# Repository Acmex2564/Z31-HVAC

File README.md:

# Z31-HVAC

This sure is a thing

36 pin board connector is TE 172023-1 Dual-Line Interlock (DLI). Same connector as on ECU. Same connector series as TCU, ASCD, Suspension Controller, DD Power Supply. 

5 pin board connector is TE 172040-1 - Multi Interlock Connector (MIC) Mk II.

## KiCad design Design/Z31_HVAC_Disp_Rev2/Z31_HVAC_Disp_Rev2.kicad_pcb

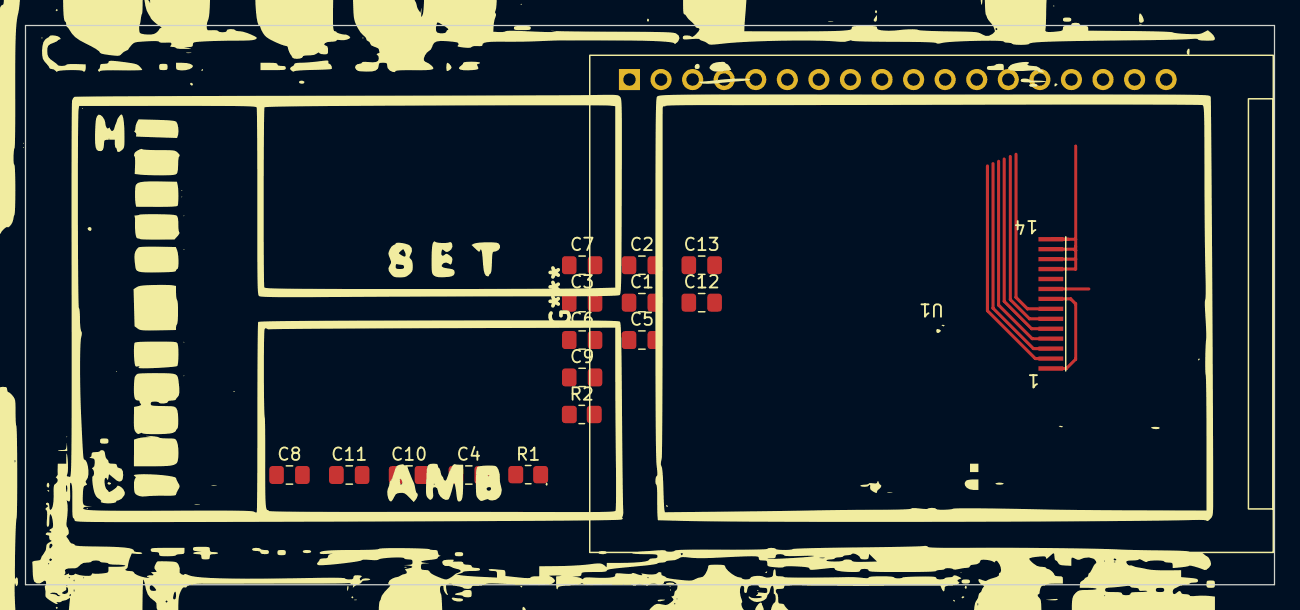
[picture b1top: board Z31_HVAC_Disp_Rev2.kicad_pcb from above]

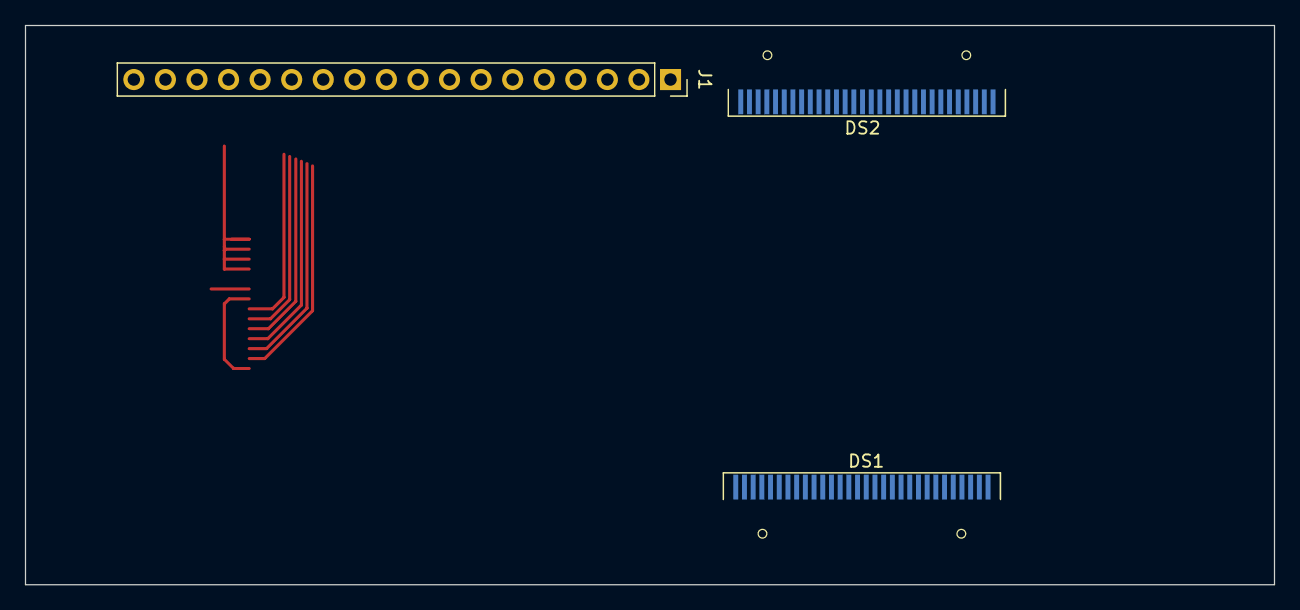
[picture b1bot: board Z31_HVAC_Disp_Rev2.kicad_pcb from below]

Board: 2 copper layers, 100.5 x 45.0 mm, 19 parts (3 on the bottom side), 26 nets.

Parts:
C1, C2, C5, C6, C8, C9, C11, C12: 1u; C_0805_2012Metric_Pad1.18x1.45mm_HandSolder
C3, C10: 4.7u; C_0805_2012Metric_Pad1.18x1.45mm_HandSolder
C4: 100n; C_0805_2012Metric_Pad1.18x1.45mm_HandSolder
C7, C13: 2.2u; C_0805_2012Metric_Pad1.18x1.45mm_HandSolder
DS1, DS2: OLED-128O064D
J1: Conn_01x18; PinSocket_1x18_P2.54mm_Vertical
R1, R2: 390k; R_0805_2012Metric_Pad1.20x1.40mm_HandSolder
U1: 2.2__WVGA_SPI_14pin; 2.2_wvga_spi

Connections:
+3V3: C4.1, C5.1, C6.1, C11.1, C12.1, DS1.6 (VBAT), DS1.9 (VDD), DS2.6 (VBAT), DS2.9 (VDD), J1.2, U1.9 (VCC)
/CS1: DS1.13 (~CS), J1.10
/CS2: DS2.13 (~CS), J1.9
/CS3: J1.8, U1.5 (CS)
/D/C: DS1.15 (D/~C), DS2.15 (D/~C), J1.6, U1.4 (D/CX)
/RESET1: DS1.14 (~RES), J1.13
/RESET2: DS2.14 (~RES), J1.12
/RESET3: J1.11, U1.2 (RESET)
/SCK: DS1.18 (D0), DS2.18 (D0), J1.3, U1.3 (SCL)
/SDI: DS1.19 (D1), DS2.19 (D1), J1.4, U1.6 (SDI)
/SDO: J1.5, U1.7 (SDO)
GND: C3.2, C4.2, C5.2, C6.2, C7.2, C10.2, C11.2, C12.2, C13.2, DS1.1 (GND), DS1.8 (VSS), DS1.10 (BS0), DS1.11 (BS1), DS1.12 (BS2), DS1.16 (R/~W), DS1.17 (E/~RD), DS1.21 (D3), DS1.22 (D4), DS1.23 (D5), DS1.24 (D6), DS1.25 (D7), DS1.29 (VLSS), DS1.30 (GND), DS2.1 (GND), DS2.8 (VSS), DS2.10 (BS0), DS2.11 (BS1), DS2.12 (BS2), DS2.16 (R/~W), DS2.17 (E/~RD), DS2.21 (D3), DS2.22 (D4), DS2.23 (D5), DS2.24 (D6), DS2.25 (D7), DS2.29 (VLSS), DS2.30 (GND), J1.1, J1.18, R1.2, R2.2, U1.1 (GND_P), U1.8 (GND), U1.11 (LEDK1), U1.12 (LEDK2), U1.13 (LEDK3), U1.14 (LEDK4)
unnamed: C1.1, DS1.2 (C2N)
unnamed: C1.2, DS1.3 (C2P)
unnamed: C2.1, DS1.4 (C1P)
unnamed: C2.2, DS1.5 (C1N)
unnamed: C3.1, DS1.27 (VCOMH)
unnamed: C7.1, DS1.28 (VCC)
unnamed: C8.1, DS2.2 (C2N)
unnamed: C8.2, DS2.3 (C2P)
unnamed: C9.1, DS2.4 (C1P)
unnamed: C9.2, DS2.5 (C1N)
unnamed: C10.1, DS2.27 (VCOMH)
unnamed: C13.1, DS2.28 (VCC)
unnamed: DS1.26 (IREF), R1.1
unnamed: DS2.26 (IREF), R2.1

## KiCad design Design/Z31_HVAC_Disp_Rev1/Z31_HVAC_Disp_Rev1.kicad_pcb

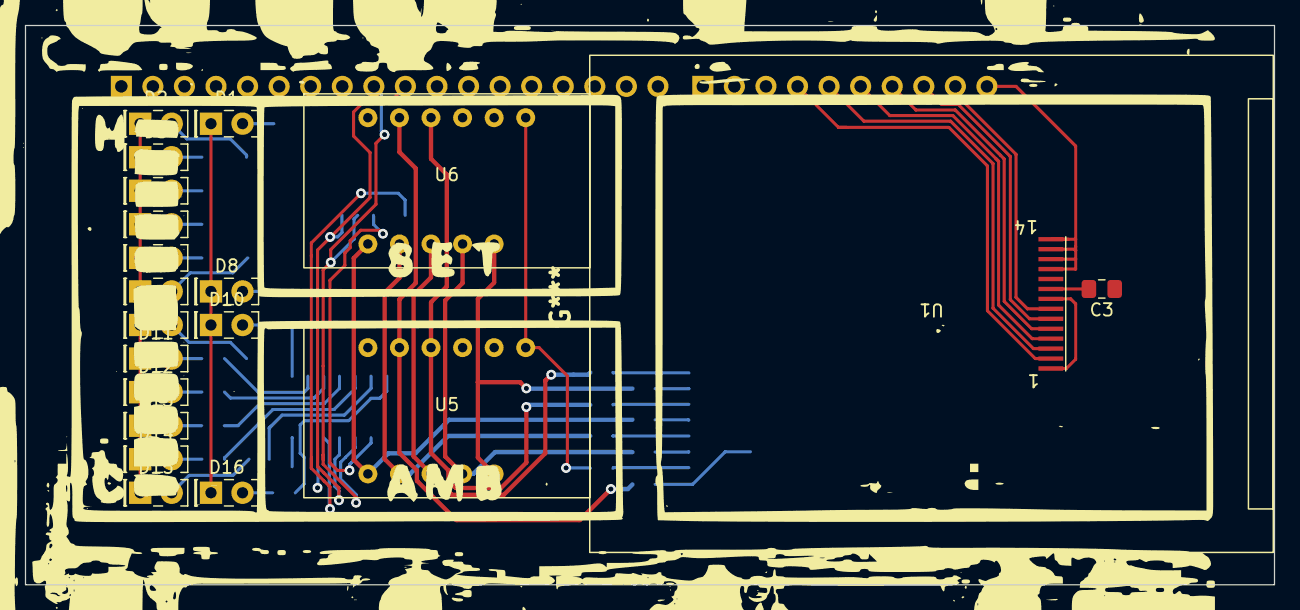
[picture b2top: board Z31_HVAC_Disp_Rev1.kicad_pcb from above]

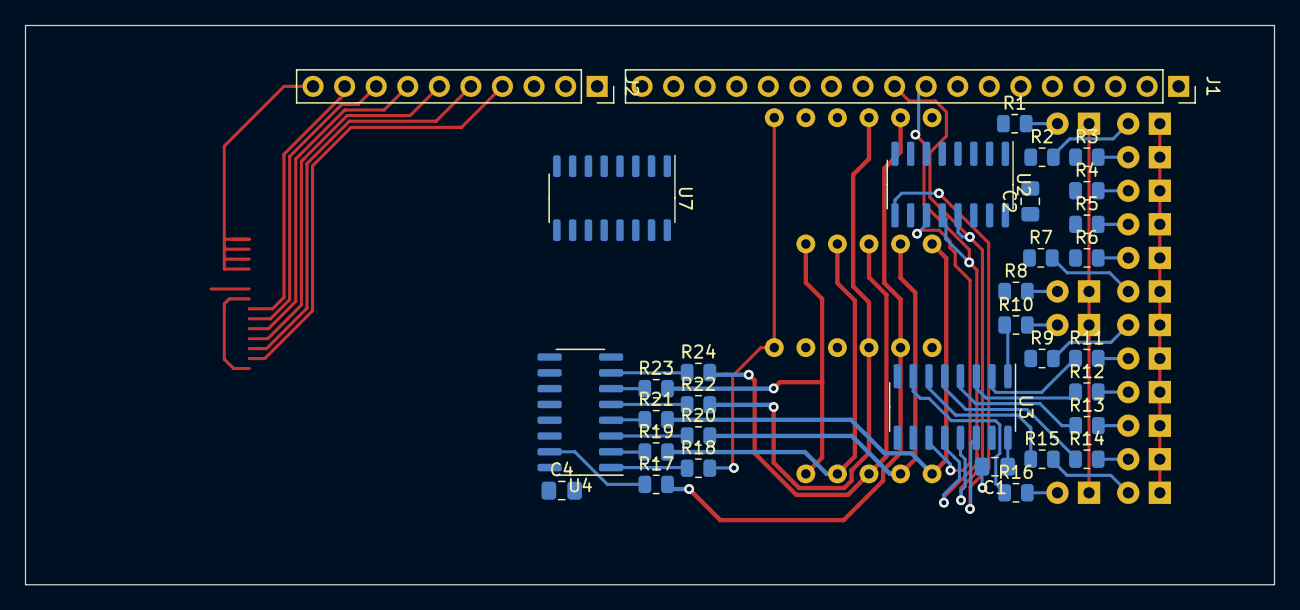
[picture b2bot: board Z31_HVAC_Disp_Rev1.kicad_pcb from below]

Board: 2 copper layers, 100.5 x 45.0 mm, 53 parts (33 on the bottom side), 79 nets.

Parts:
C1, C2, C3, C4: 100n; C_0805_2012Metric_Pad1.18x1.45mm_HandSolder
D1, D2, D3, D4, D5, D6, D7, D8, D9, D10, D11, D12, D13, D14, D15, D16: LED; LED_Rectangular_W5.0mm_H2.0mm
J1: Conn_01x18; PinSocket_1x18_P2.54mm_Vertical
J2: Conn_01x10; PinSocket_1x10_P2.54mm_Vertical
R1, R2, R3, R4, R5, R6, R7, R8, R9, R10, R11, R12, R13, R14, R15, R16, R17, R18, R19, R20, R21, R22, R23, R24: 220; R_0805_2012Metric
U1: 2.2__WVGA_SPI_14pin; 2.2_wvga_spi
U2, U3, U4: 74HC595; SOIC-16_3.9x9.9mm_P1.27mm
U5, U6: CL3631AH
U7: ULN2003; SO-16_3.9x9.9mm_P1.27mm

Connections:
+5V: C1.1, C2.1, C4.1, J1.2, U2.16 (VCC), U3.16 (VCC), U4.16 (VCC)
/Clear: J1.5, U2.10 (~SRCLR), U3.10 (~SRCLR), U4.10 (~SRCLR)
/D1: J1.11, U7.1 (I1)
/D2: J1.12, U7.2 (I2)
/D3: J1.13, U7.3 (I3)
/D4: J1.14, U7.4 (I4)
/D5: J1.15, U7.5 (I5)
/D6: J1.16, U7.6 (I6)
/LED_Dimming: J1.10, U2.13 (~OE), U3.13 (~OE), U4.13 (~OE)
/LH_1: J1.9, U2.12 (RCLK), U3.12 (RCLK)
/LH_2: J1.6, U4.12 (RCLK)
/MOSI_1: J1.7, U2.14 (SER)
/MOSI_2: J1.3, U4.14 (SER)
/SCK_1: J1.8, U2.11 (SRCLK), U3.11 (SRCLK)
/SCK_2: J1.4, U4.11 (SRCLK)
GND: C1.2, C2.2, C3.1, C4.2, D1.1 (K), D2.1 (K), D3.1 (K), D4.1 (K), D5.1 (K), D6.1 (K), D7.1 (K), D8.1 (K), D9.1 (K), D10.1 (K), D11.1 (K), D12.1 (K), D13.1 (K), D14.1 (K), D15.1 (K), D16.1 (K), J1.1, J1.18, J2.1, J2.10, U1.1 (GND_P), U1.8 (GND), U1.11 (LEDK1), U1.12 (LEDK2), U1.13 (LEDK3), U1.14 (LEDK4), U2.8 (GND), U3.8 (GND), U4.8 (GND), U7.8 (GND)
unnamed: C3.2, J2.2, U1.9 (VCC)
unnamed: D1.2 (A), R1.2
unnamed: D2.2 (A), R2.2
unnamed: D3.2 (A), R3.2
unnamed: D4.2 (A), R4.2
unnamed: D5.2 (A), R5.2
unnamed: D6.2 (A), R6.2
unnamed: D7.2 (A), R7.2
unnamed: D8.2 (A), R8.2
unnamed: D9.2 (A), R9.2
unnamed: D10.2 (A), R10.2
unnamed: D11.2 (A), R11.2
unnamed: D12.2 (A), R12.2
unnamed: D13.2 (A), R13.2
unnamed: D14.2 (A), R14.2
unnamed: D15.2 (A), R15.2
unnamed: D16.2 (A), R16.2
unnamed: J2.3, U1.10 (LEDA)
unnamed: J2.4, U1.2 (RESET)
unnamed: J2.5, U1.3 (SCL)
unnamed: J2.6, U1.4 (D/CX)
unnamed: J2.7, U1.5 (CS)
unnamed: J2.8, U1.6 (SDI)
unnamed: J2.9, U1.7 (SDO)
unnamed: R1.1, U2.15 (QA)
unnamed: R2.1, U2.1 (QB)
unnamed: R3.1, U2.2 (QC)
unnamed: R4.1, U2.3 (QD)
unnamed: R5.1, U2.4 (QE)
unnamed: R6.1, U2.5 (QF)
unnamed: R7.1, U2.6 (QG)
unnamed: R8.1, U2.7 (QH)
unnamed: R9.1, U3.15 (QA)
unnamed: R10.1, U3.1 (QB)
unnamed: R11.1, U3.2 (QC)
unnamed: R12.1, U3.3 (QD)
unnamed: R13.1, U3.4 (QE)
unnamed: R14.1, U3.5 (QF)
unnamed: R15.1, U3.6 (QG)
unnamed: R16.1, U3.7 (QH)
unnamed: R17.1, U4.15 (QA)
unnamed: R17.2, U5.11 (ANODE_A), U6.11 (ANODE_A)
unnamed: R18.1, U4.1 (QB)
unnamed: R18.2, U5.7 (ANODE_B), U6.7 (ANODE_B)
unnamed: R19.1, U4.2 (QC)
unnamed: R19.2, U5.4 (ANODE_C), U6.4 (ANODE_C)
unnamed: R20.1, U4.3 (QD)
unnamed: R20.2, U5.2 (ANODE_D), U6.2 (ANODE_D)
unnamed: R21.1, U4.4 (QE)
unnamed: R21.2, U5.1 (ANODE_E), U6.1 (ANODE_E)
unnamed: R22.1, U4.5 (QF)
unnamed: R22.2, U5.10 (ANODE_F), U6.10 (ANODE_F)
unnamed: R23.1, U4.6 (QG)
unnamed: R23.2, U5.5 (ANODE_G), U6.5 (ANODE_G)
unnamed: R24.1, U4.7 (QH)
unnamed: R24.2, U5.3 (ANODE_DP), U6.3 (ANODE_DP)
unnamed: U2.9 (QH'), U3.14 (SER)
unnamed: U5.8 (CATHODE_3), U7.16 (O1)
unnamed: U5.9 (CATHODE_2), U7.15 (O2)
unnamed: U5.12 (CATHODE_1), U7.14 (O3)
unnamed: U6.8 (CATHODE_3), U7.13 (O4)
unnamed: U6.9 (CATHODE_2), U7.12 (O5)
unnamed: U6.12 (CATHODE_1), U7.11 (O6)

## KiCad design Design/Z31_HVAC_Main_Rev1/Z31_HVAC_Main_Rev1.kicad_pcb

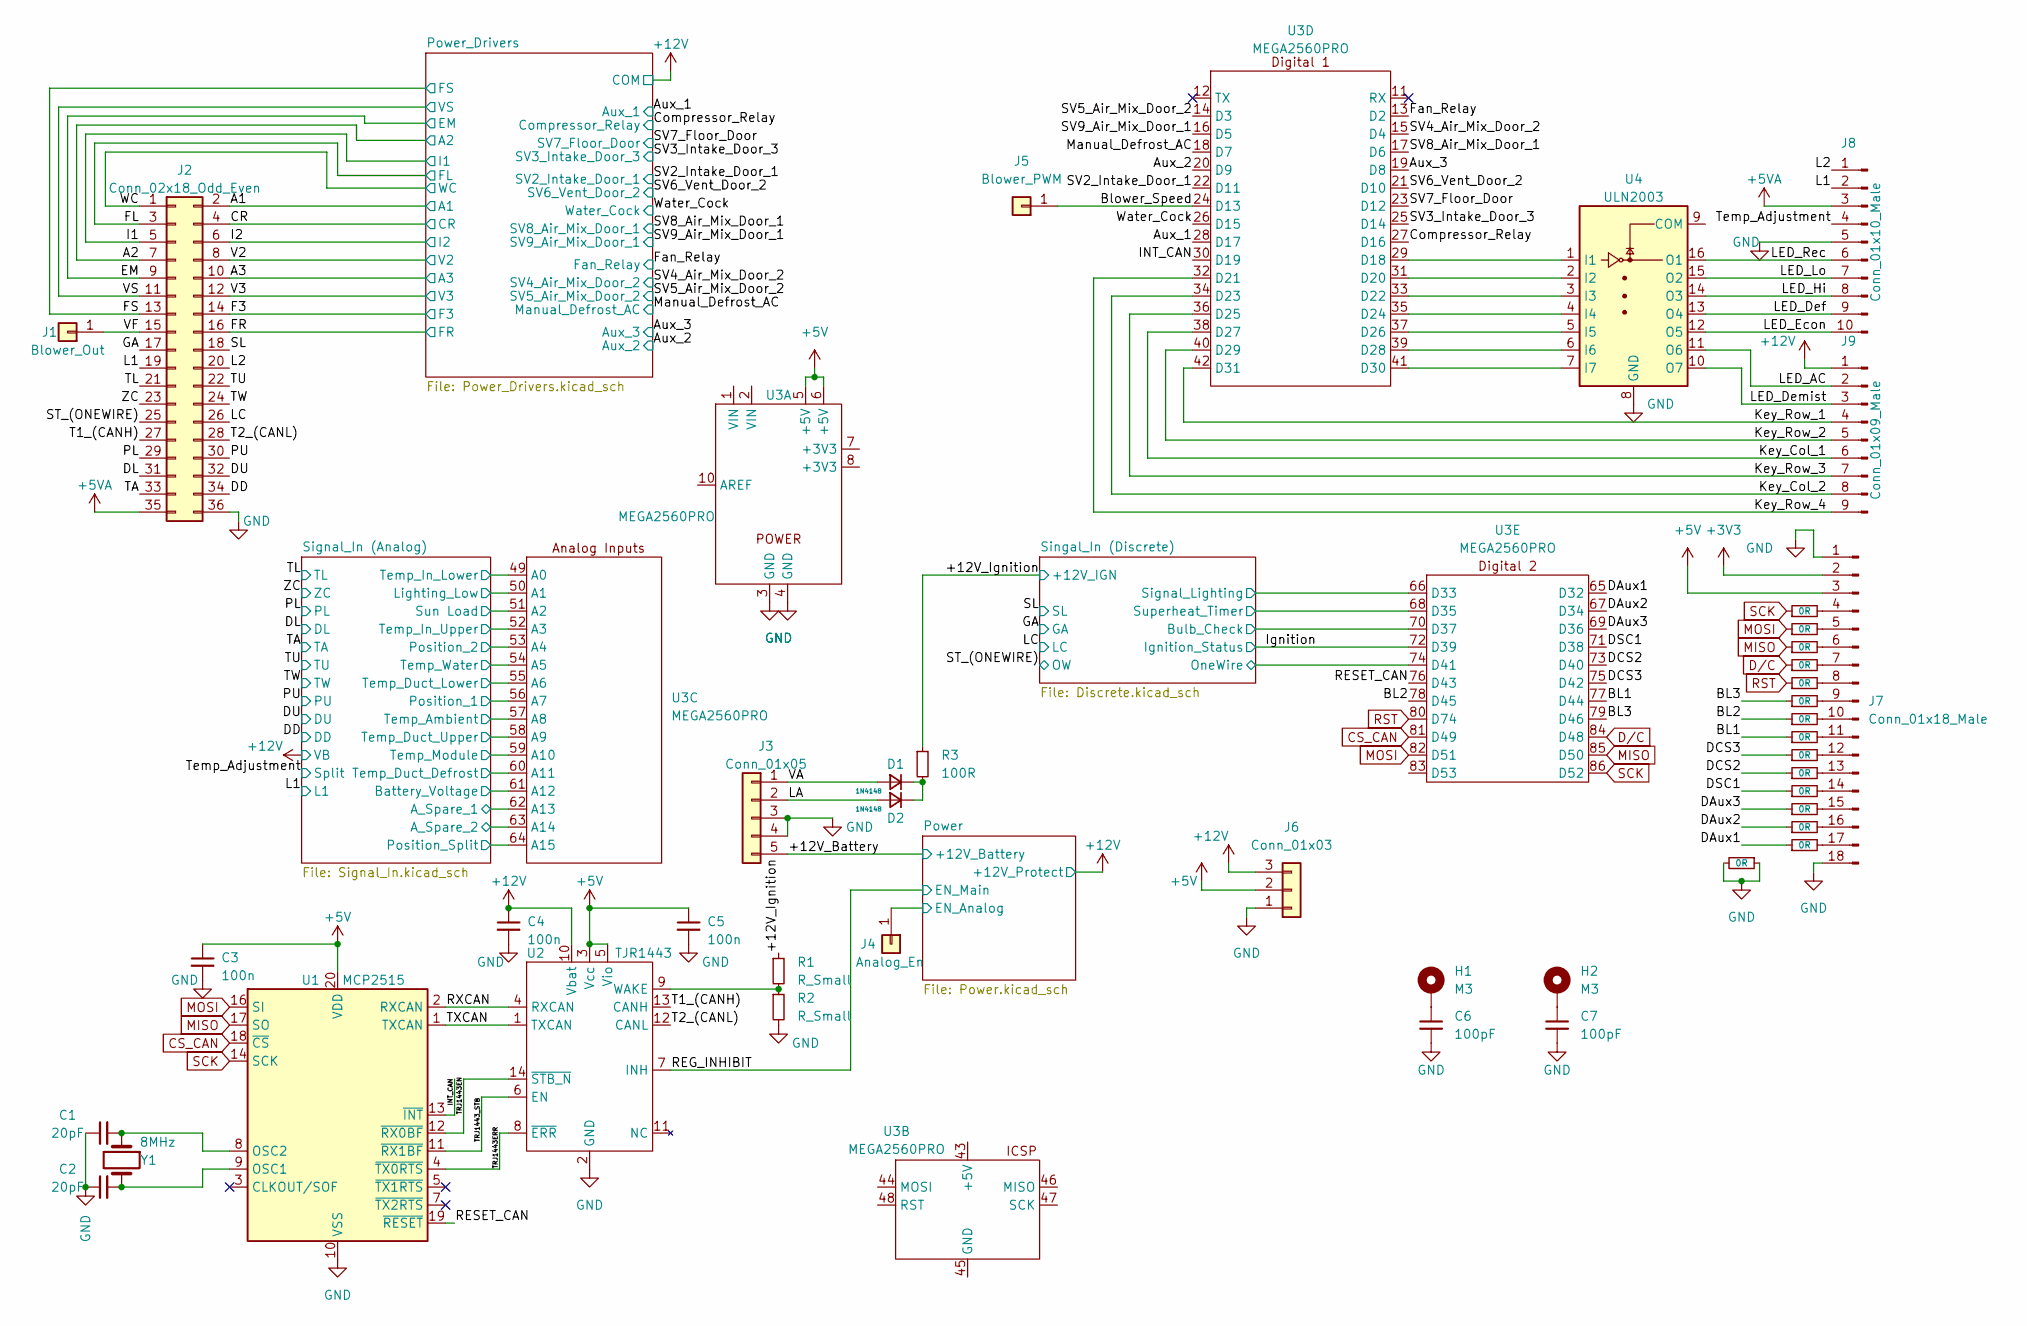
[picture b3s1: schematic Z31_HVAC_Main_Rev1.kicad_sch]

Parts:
C1, C2: 20pF; C_0805_2012Metric_Pad1.18x1.45mm_HandSolder
C3, C4, C5: 100n; C_0805_2012Metric_Pad1.18x1.45mm_HandSolder
C6, C7: 100pF; C_0805_2012Metric_Pad1.18x1.45mm_HandSolder
D1, D2: 1N4148; D_SOD-323_HandSoldering
H1, H2: M3; MountingHole_3.5mm_Pad
J1: Blower_Out; PinHeader_1x01_P2.54mm_Vertical
J2: Conn_02x18_Odd_Even; TE-172023
J3: Conn_01x05; Z31_HVAC_Connector_1
J4: Analog_En; PinHeader_1x01_P2.54mm_Vertical
J5: Blower_PWM; PinHeader_1x01_P2.54mm_Vertical
J6: Conn_01x03; Proto-Area
J7: Conn_01x18_Male; PinHeader_1x18_P2.54mm_Vertical
J8: Conn_01x10_Male; PinHeader_1x10_P2.54mm_Vertical
J9: Conn_01x09_Male; PinHeader_1x09_P2.54mm_Vertical
R1, R2: R_Small; R_0805_2012Metric_Pad1.20x1.40mm_HandSolder
R3: 100R; R_Axial_DIN0207_L6.3mm_D2.5mm_P7.62mm_Horizontal
R4, R5, R6, R7, R8, R9, R10, R11, R12, R13, R14, R15, R16, R17, R18: 0R; R_Axial_DIN0204_L3.6mm_D1.6mm_P2.54mm_Vertical
U1: MCP2515; TSSOP-20_4.4x6.5mm_P0.65mm
U2: TJR1443; SO-14_3.9x8.65mm_P1.27mm
U3: MEGA2560PRO
U4: ULN2003; SO-16_3.9x9.9mm_P1.27mm
Y1: 8MHz; Crystal_SMD_HC49-SD

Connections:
+3V3: J7.2
+5V: C3.1, C5.1, J6.2, J7.3, U1.20 (VDD), U2.3 (Vcc), U2.5 (Vio), U3.5 (+5V), U3.6 (+5V); also elsewhere on the board
+5VA: J2.35, J8.3; also elsewhere on the board
+12V: C4.1, J6.3, J9.1, U2.10 (Vbat); also elsewhere on the board
/+12V_Battery: J3.5; also elsewhere on the board
/+12V_Ignition: R1.1, R3.1; also elsewhere on the board
/A1: J2.2; also elsewhere on the board
/A2: J2.7; also elsewhere on the board
/A3: J2.10; also elsewhere on the board
/Aux_1: U3.28 (D17); also elsewhere on the board
/Aux_2: U3.20 (D9); also elsewhere on the board
/Aux_3: U3.19 (D8); also elsewhere on the board
/BL1: R12.1, U3.77 (D44)
/BL2: R11.1, U3.78 (D45)
/BL3: R10.1, U3.79 (D46)
/Blower_Speed: J5.1, U3.24 (D13)
/CR: J2.4; also elsewhere on the board
/Compressor_Relay: U3.27 (D16); also elsewhere on the board
/DAux1: R18.1, U3.65 (D32)
/DAux2: R17.1, U3.67 (D34)
/DAux3: R16.1, U3.69 (D36)
/DCS2: R14.1, U3.73 (D40)
/DCS3: R13.1, U3.75 (D42)
/DD: J2.34; also elsewhere on the board
/DL: J2.31; also elsewhere on the board
/DSC1: R15.1, U3.71 (D38)
/DU: J2.32; also elsewhere on the board
/EM: J2.9; also elsewhere on the board
/F3: J2.14; also elsewhere on the board
/FL: J2.3; also elsewhere on the board
/FR: J2.16; also elsewhere on the board
/FS: J2.13; also elsewhere on the board
/Fan_Relay: U3.13 (D2); also elsewhere on the board
/GA: J2.17; also elsewhere on the board
/I1: J2.5; also elsewhere on the board
/I2: J2.6; also elsewhere on the board
/INT_CAN: U1.13 (~INT), U3.30 (D19)
/Ignition: U3.72 (D39); also elsewhere on the board
/Key_Col_1: J9.6, U3.38 (D27)
/Key_Col_2: J9.8, U3.34 (D23)
/Key_Row_1: J9.4, U3.42 (D31)
/Key_Row_2: J9.5, U3.40 (D29)
/Key_Row_3: J9.7, U3.36 (D25)
/Key_Row_4: J9.9, U3.32 (D21)
/L1: J2.19, J8.2; also elsewhere on the board
/L2: J2.20, J8.1
/LA: D2.2 (A), J3.2
/LC: J2.26; also elsewhere on the board
/LED_AC: J9.2, U4.11 (O6)
/LED_Def: J8.9, U4.13 (O4)
/LED_Demist: J9.3, U4.10 (O7)
/LED_Econ: J8.10, U4.12 (O5)
/LED_Hi: J8.8, U4.14 (O3)
/LED_Lo: J8.7, U4.15 (O2)
/LED_Rec: J8.6, U4.16 (O1)
/Manual_Defrost_AC: U3.18 (D7); also elsewhere on the board
/PL: J2.29; also elsewhere on the board
/PU: J2.30; also elsewhere on the board
/Power/EN_Analog: J4.1; also elsewhere on the board
/REG_INHIBIT: U2.7 (INH); also elsewhere on the board
/RESET_CAN: U1.19 (~RESET), U3.76 (D43)
/RXCAN: U1.2 (RXCAN), U2.4 (RXCAN)
/SL: J2.18; also elsewhere on the board
/ST_(ONEWIRE): J2.25; also elsewhere on the board
/SV2_Intake_Door_1: U3.22 (D11); also elsewhere on the board
/SV3_Intake_Door_3: U3.25 (D14); also elsewhere on the board
/SV4_Air_Mix_Door_2: U3.15 (D4); also elsewhere on the board
/SV5_Air_Mix_Door_2: U3.14 (D3); also elsewhere on the board
/SV6_Vent_Door_2: U3.21 (D10); also elsewhere on the board
/SV7_Floor_Door: U3.23 (D12); also elsewhere on the board
/SV8_Air_Mix_Door_1: U3.17 (D6); also elsewhere on the board
/SV9_Air_Mix_Door_1: U3.16 (D5); also elsewhere on the board
/Signal_In (Analog)/A_Spare_1: U3.62 (A13); also elsewhere on the board
/Signal_In (Analog)/A_Spare_2: U3.63 (A14); also elsewhere on the board
/Signal_In (Analog)/Battery_Voltage: U3.61 (A12); also elsewhere on the board
/Signal_In (Analog)/Lighting_Low: U3.50 (A1); also elsewhere on the board
/Signal_In (Analog)/Position_1: U3.56 (A7); also elsewhere on the board
/Signal_In (Analog)/Position_2: U3.53 (A4); also elsewhere on the board
/Signal_In (Analog)/Position_Split: U3.64 (A15); also elsewhere on the board
/Signal_In (Analog)/Sun Load: U3.51 (A2); also elsewhere on the board
/Signal_In (Analog)/Temp_Ambient: U3.57 (A8); also elsewhere on the board
/Signal_In (Analog)/Temp_Duct_Defrost: U3.60 (A11); also elsewhere on the board
/Signal_In (Analog)/Temp_Duct_Lower: U3.55 (A6); also elsewhere on the board
/Signal_In (Analog)/Temp_Duct_Upper: U3.58 (A9); also elsewhere on the board
/Signal_In (Analog)/Temp_In_Lower: U3.49 (A0); also elsewhere on the board
/Signal_In (Analog)/Temp_In_Upper: U3.52 (A3); also elsewhere on the board
/Signal_In (Analog)/Temp_Module: U3.59 (A10); also elsewhere on the board
/Signal_In (Analog)/Temp_Water: U3.54 (A5); also elsewhere on the board
/Singal_In (Discrete)/Bulb_Check: U3.70 (D37); also elsewhere on the board
/Singal_In (Discrete)/OneWire: U3.74 (D41); also elsewhere on the board
/Singal_In (Discrete)/Signal_Lighting: U3.66 (D33); also elsewhere on the board
/Singal_In (Discrete)/Superheat_Timer: U3.68 (D35); also elsewhere on the board
/T1_(CANH): J2.27, U2.13 (CANH)
/T2_(CANL): J2.28, U2.12 (CANL)
/TA: J2.33; also elsewhere on the board
/TL: J2.21; also elsewhere on the board
/TRJ1443EN: U1.12 (~RX0BF), U2.14 (~STB_N)
/TRJ1443ERR: U1.4 (~TX0RTS), U2.8 (~ERR)
/TRJ1443_STB: U1.11 (~RX1BF), U2.6 (EN)
/TU: J2.22; also elsewhere on the board
/TW: J2.24; also elsewhere on the board
/TXCAN: U1.1 (TXCAN), U2.1 (TXCAN)
/Temp_Adjustment: J8.4; also elsewhere on the board
/V2: J2.8; also elsewhere on the board
/V3: J2.12; also elsewhere on the board
/VA: D1.2 (A), J3.1
/VF: J1.1, J2.15
/VS: J2.11; also elsewhere on the board
/WC: J2.1; also elsewhere on the board
/Water_Cock: U3.26 (D15); also elsewhere on the board
/ZC: J2.23; also elsewhere on the board
CS_CAN: U1.18 (~CS), U3.81 (D49)
D/C: R8.1, U3.84 (D48)
GND: C1.1, C2.1, C3.2, C4.2, C5.2, C6.2, C7.2, J2.36, J3.3, J3.4, J6.1, J7.1, J7.18, J8.5, R2.2, R4.1, R4.2, U1.10 (VSS), U2.2 (GND), U3.3 (GND), U3.4 (GND), U4.8 (GND); also elsewhere on the board
MISO: R7.1, U1.17 (SO), U3.85 (D50)
MOSI: R6.1, U1.16 (SI), U3.82 (D51)
unnamed: C1.2, U1.8 (OSC2), Y1.1
unnamed: C2.2, U1.9 (OSC1), Y1.2
unnamed: C6.1, H1.1
unnamed: C7.1, H2.1
unnamed: D1.1 (K), D2.1 (K), R3.2
unnamed: J7.4, R5.2
unnamed: J7.5, R6.2
unnamed: J7.6, R7.2
unnamed: J7.7, R8.2
unnamed: J7.8, R9.2
unnamed: J7.9, R10.2
unnamed: J7.10, R11.2
unnamed: J7.11, R12.2
unnamed: J7.12, R13.2
unnamed: J7.13, R14.2
unnamed: J7.14, R15.2
unnamed: J7.15, R16.2
unnamed: J7.16, R17.2
unnamed: J7.17, R18.2
unnamed: R1.2, R2.1, U2.9 (WAKE)
unnamed: U3.29 (D18), U4.1 (I1)
unnamed: U3.31 (D20), U4.2 (I2)
unnamed: U3.33 (D22), U4.3 (I3)
unnamed: U3.35 (D24), U4.4 (I4)
unnamed: U3.37 (D26), U4.5 (I5)
unnamed: U3.39 (D28), U4.6 (I6)
unnamed: U3.41 (D30), U4.7 (I7)
RST: R9.1, U3.80 (D74)
SCK: R5.1, U1.14 (SCK), U3.86 (D52)

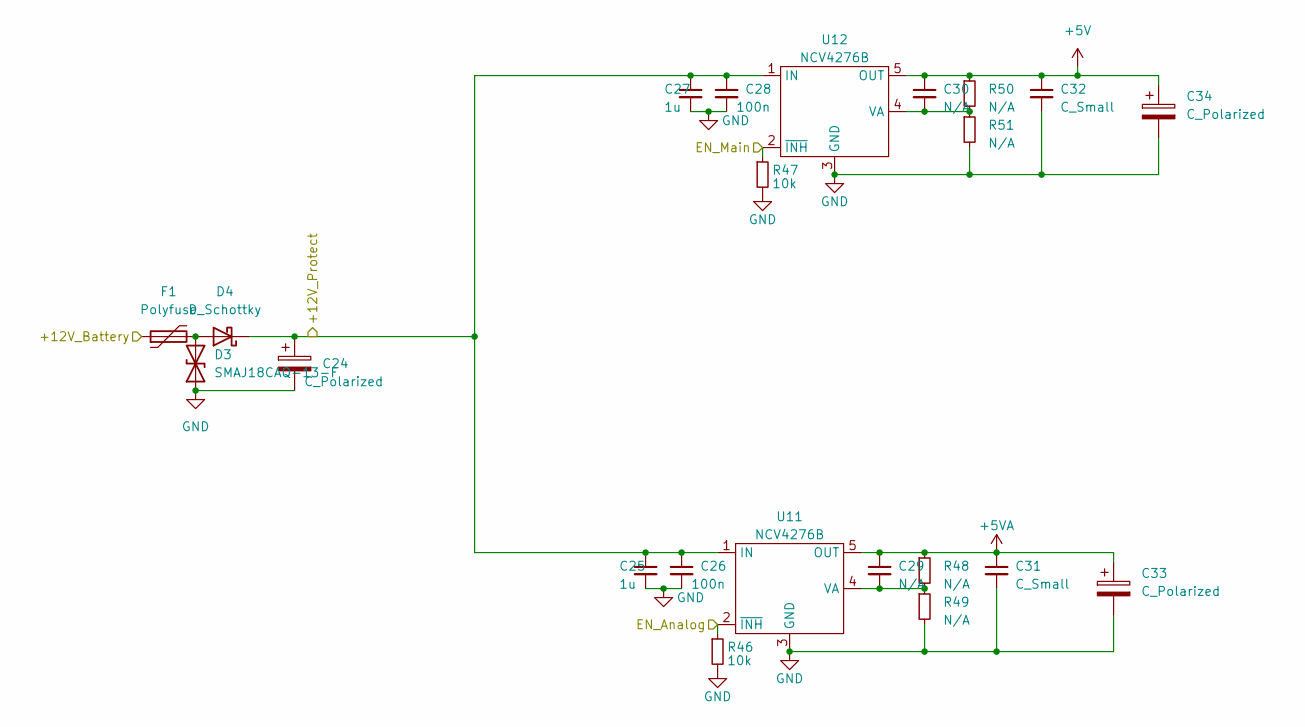
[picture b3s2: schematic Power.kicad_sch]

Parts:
C24: C_Polarized; CP_Radial_D8.0mm_P3.50mm
C25, C27: 1u; C_1210_3225Metric_Pad1.33x2.70mm_HandSolder
C26, C28: 100n; C_0805_2012Metric_Pad1.18x1.45mm_HandSolder
C29, C30: N/A; C_0805_2012Metric_Pad1.18x1.45mm_HandSolder
C31, C32: C_Small; C_1210_3225Metric_Pad1.33x2.70mm_HandSolder
C33, C34: C_Polarized; CP_Elec_5x5.3
D3: SMAJ18CAQ-13-F; D_SMA
D4: D_Schottky; D_SMA
F1: Polyfuse; Fuse_1812_4532Metric_Pad1.30x3.40mm_HandSolder
R46, R47: 10k; R_0805_2012Metric_Pad1.20x1.40mm_HandSolder
R48, R49, R50, R51: N/A; R_0805_2012Metric_Pad1.20x1.40mm_HandSolder
U11, U12: NCV4276B; TO-263-5_TabPin3

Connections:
+5V: C30.1, C32.1, C34.1, R50.1, U12.5 (OUT); also elsewhere on the board
+5VA: C29.1, C31.1, C33.1, R48.1, U11.5 (OUT); also elsewhere on the board
+12V: C24.1, C25.1, C26.1, C27.1, C28.1, D4.1 (K), U11.1 (IN), U12.1 (IN); also elsewhere on the board
/+12V_Battery: F1.1; also elsewhere on the board
/Power/EN_Analog: R46.1, U11.2 (~INH); also elsewhere on the board
/REG_INHIBIT: R47.1, U12.2 (~INH); also elsewhere on the board
GND: C24.2, C25.2, C26.2, C27.2, C28.2, C31.2, C32.2, C33.2, C34.2, D3.1 (A1), R46.2, R47.2, R49.2, R51.2, U11.3 (GND), U12.3 (GND); also elsewhere on the board
unnamed: C29.2, R48.2, R49.1, U11.4 (VA)
unnamed: C30.2, R50.2, R51.1, U12.4 (VA)
unnamed: D3.2 (A2), D4.2 (A), F1.2

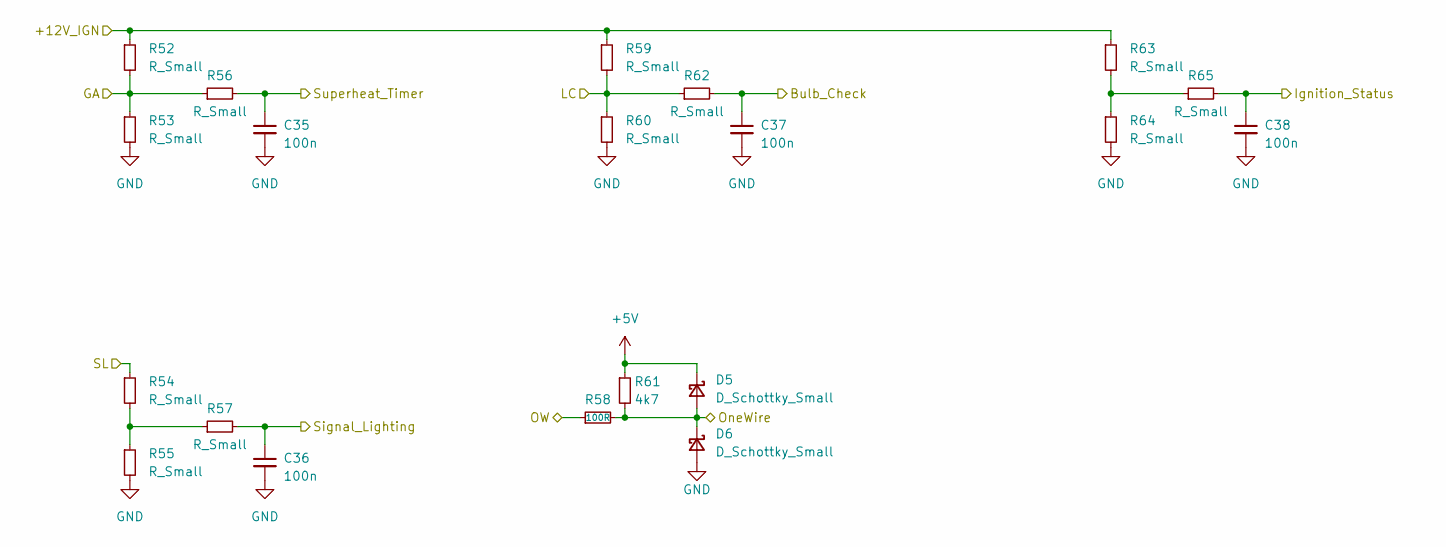
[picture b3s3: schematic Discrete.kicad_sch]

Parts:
C35, C36, C37, C38: 100n; C_0805_2012Metric_Pad1.18x1.45mm_HandSolder
D5, D6: D_Schottky_Small; D_SOD-323_HandSoldering
R52, R53, R54, R55, R56, R57, R59, R60, R62, R63, R64, R65: R_Small; R_0805_2012Metric_Pad1.20x1.40mm_HandSolder
R58: 100R; R_0805_2012Metric_Pad1.20x1.40mm_HandSolder
R61: 4k7; R_0805_2012Metric_Pad1.20x1.40mm_HandSolder

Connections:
+5V: D5.1 (K), R61.1; also elsewhere on the board
/+12V_Ignition: R52.1, R59.1, R63.1; also elsewhere on the board
/GA: R52.2, R53.1, R56.1; also elsewhere on the board
/Ignition: C38.1, R65.2; also elsewhere on the board
/LC: R59.2, R60.1, R62.1; also elsewhere on the board
/SL: R54.1; also elsewhere on the board
/ST_(ONEWIRE): R58.1; also elsewhere on the board
/Singal_In (Discrete)/Bulb_Check: C37.1, R62.2; also elsewhere on the board
/Singal_In (Discrete)/OneWire: D5.2 (A), D6.1 (K), R58.2, R61.2; also elsewhere on the board
/Singal_In (Discrete)/Signal_Lighting: C36.1, R57.2; also elsewhere on the board
/Singal_In (Discrete)/Superheat_Timer: C35.1, R56.2; also elsewhere on the board
GND: C35.2, C36.2, C37.2, C38.2, D6.2 (A), R53.2, R55.2, R60.2, R64.2; also elsewhere on the board
unnamed: R54.2, R55.1, R57.1
unnamed: R63.2, R64.1, R65.1

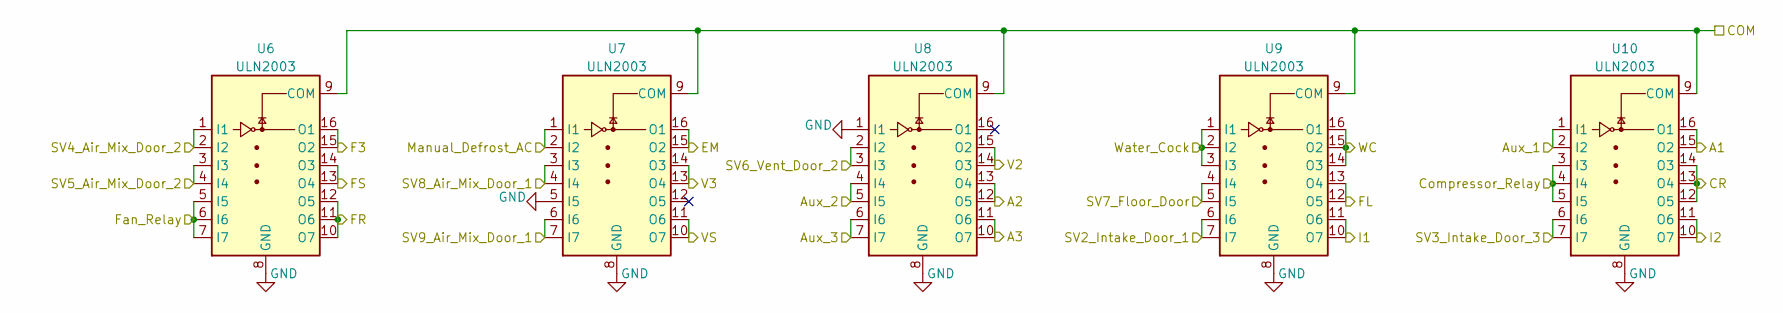
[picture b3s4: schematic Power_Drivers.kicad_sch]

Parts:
U6, U7, U8, U9, U10: ULN2003; SO-16_3.9x9.9mm_P1.27mm

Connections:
+12V: U6.9 (COM), U7.9 (COM), U8.9 (COM), U9.9 (COM), U10.9 (COM); also elsewhere on the board
/A1: U10.15 (O2), U10.16 (O1); also elsewhere on the board
/A2: U8.12 (O5), U8.13 (O4); also elsewhere on the board
/A3: U8.10 (O7), U8.11 (O6); also elsewhere on the board
/Aux_1: U10.1 (I1), U10.2 (I2); also elsewhere on the board
/Aux_2: U8.4 (I4), U8.5 (I5); also elsewhere on the board
/Aux_3: U8.6 (I6), U8.7 (I7); also elsewhere on the board
/CR: U10.12 (O5), U10.13 (O4), U10.14 (O3); also elsewhere on the board
/Compressor_Relay: U10.3 (I3), U10.4 (I4), U10.5 (I5); also elsewhere on the board
/EM: U7.15 (O2), U7.16 (O1); also elsewhere on the board
/F3: U6.15 (O2), U6.16 (O1); also elsewhere on the board
/FL: U9.12 (O5), U9.13 (O4); also elsewhere on the board
/FR: U6.10 (O7), U6.11 (O6), U6.12 (O5); also elsewhere on the board
/FS: U6.13 (O4), U6.14 (O3); also elsewhere on the board
/Fan_Relay: U6.5 (I5), U6.6 (I6), U6.7 (I7); also elsewhere on the board
/I1: U9.10 (O7), U9.11 (O6); also elsewhere on the board
/I2: U10.10 (O7), U10.11 (O6); also elsewhere on the board
/Manual_Defrost_AC: U7.1 (I1), U7.2 (I2); also elsewhere on the board
/SV2_Intake_Door_1: U9.6 (I6), U9.7 (I7); also elsewhere on the board
/SV3_Intake_Door_3: U10.6 (I6), U10.7 (I7); also elsewhere on the board
/SV4_Air_Mix_Door_2: U6.1 (I1), U6.2 (I2); also elsewhere on the board
/SV5_Air_Mix_Door_2: U6.3 (I3), U6.4 (I4); also elsewhere on the board
/SV6_Vent_Door_2: U8.2 (I2), U8.3 (I3); also elsewhere on the board
/SV7_Floor_Door: U9.4 (I4), U9.5 (I5); also elsewhere on the board
/SV8_Air_Mix_Door_1: U7.3 (I3), U7.4 (I4); also elsewhere on the board
/SV9_Air_Mix_Door_1: U7.6 (I6), U7.7 (I7); also elsewhere on the board
/V2: U8.14 (O3), U8.15 (O2); also elsewhere on the board
/V3: U7.13 (O4), U7.14 (O3); also elsewhere on the board
/VS: U7.10 (O7), U7.11 (O6); also elsewhere on the board
/WC: U9.14 (O3), U9.15 (O2), U9.16 (O1); also elsewhere on the board
/Water_Cock: U9.1 (I1), U9.2 (I2), U9.3 (I3); also elsewhere on the board
GND: U6.8 (GND), U7.5 (I5), U7.8 (GND), U8.1 (I1), U8.8 (GND), U9.8 (GND), U10.8 (GND); also elsewhere on the board
